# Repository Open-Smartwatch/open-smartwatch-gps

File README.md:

# Open-Smartwatch KiCAD files

Repo for kicad schematic, board and gerber files. This project is in development and is not ready for release.

Update 2025-06: There never was a release since the selected GPS module does not work on a wearable-sized PCB, and while worn at the same time.

## Tools

To view/modify the files from this repository, install KiCAD from: [https://kicad.org](https://kicad.org)

Also, add the following Symbol/Footprint library to KiCAD: [https://github.com/Open-Smartwatch/Kicad-Libraries](https://github.com/Open-Smartwatch/Kicad-Libraries)

## Schematic

## Plots

## BOM

See: [https://htmlpreview.github.io/?https://github.com/Open-Smartwatch/kicad-project/blob/master/docs/bom/osw-ibom_v.html](https://htmlpreview.github.io/?https://github.com/Open-Smartwatch/kicad-project/blob/master/docs/bom/osw-ibom_v.html)

## Instagram 
https://www.instagram.com/pauls_3d_things/

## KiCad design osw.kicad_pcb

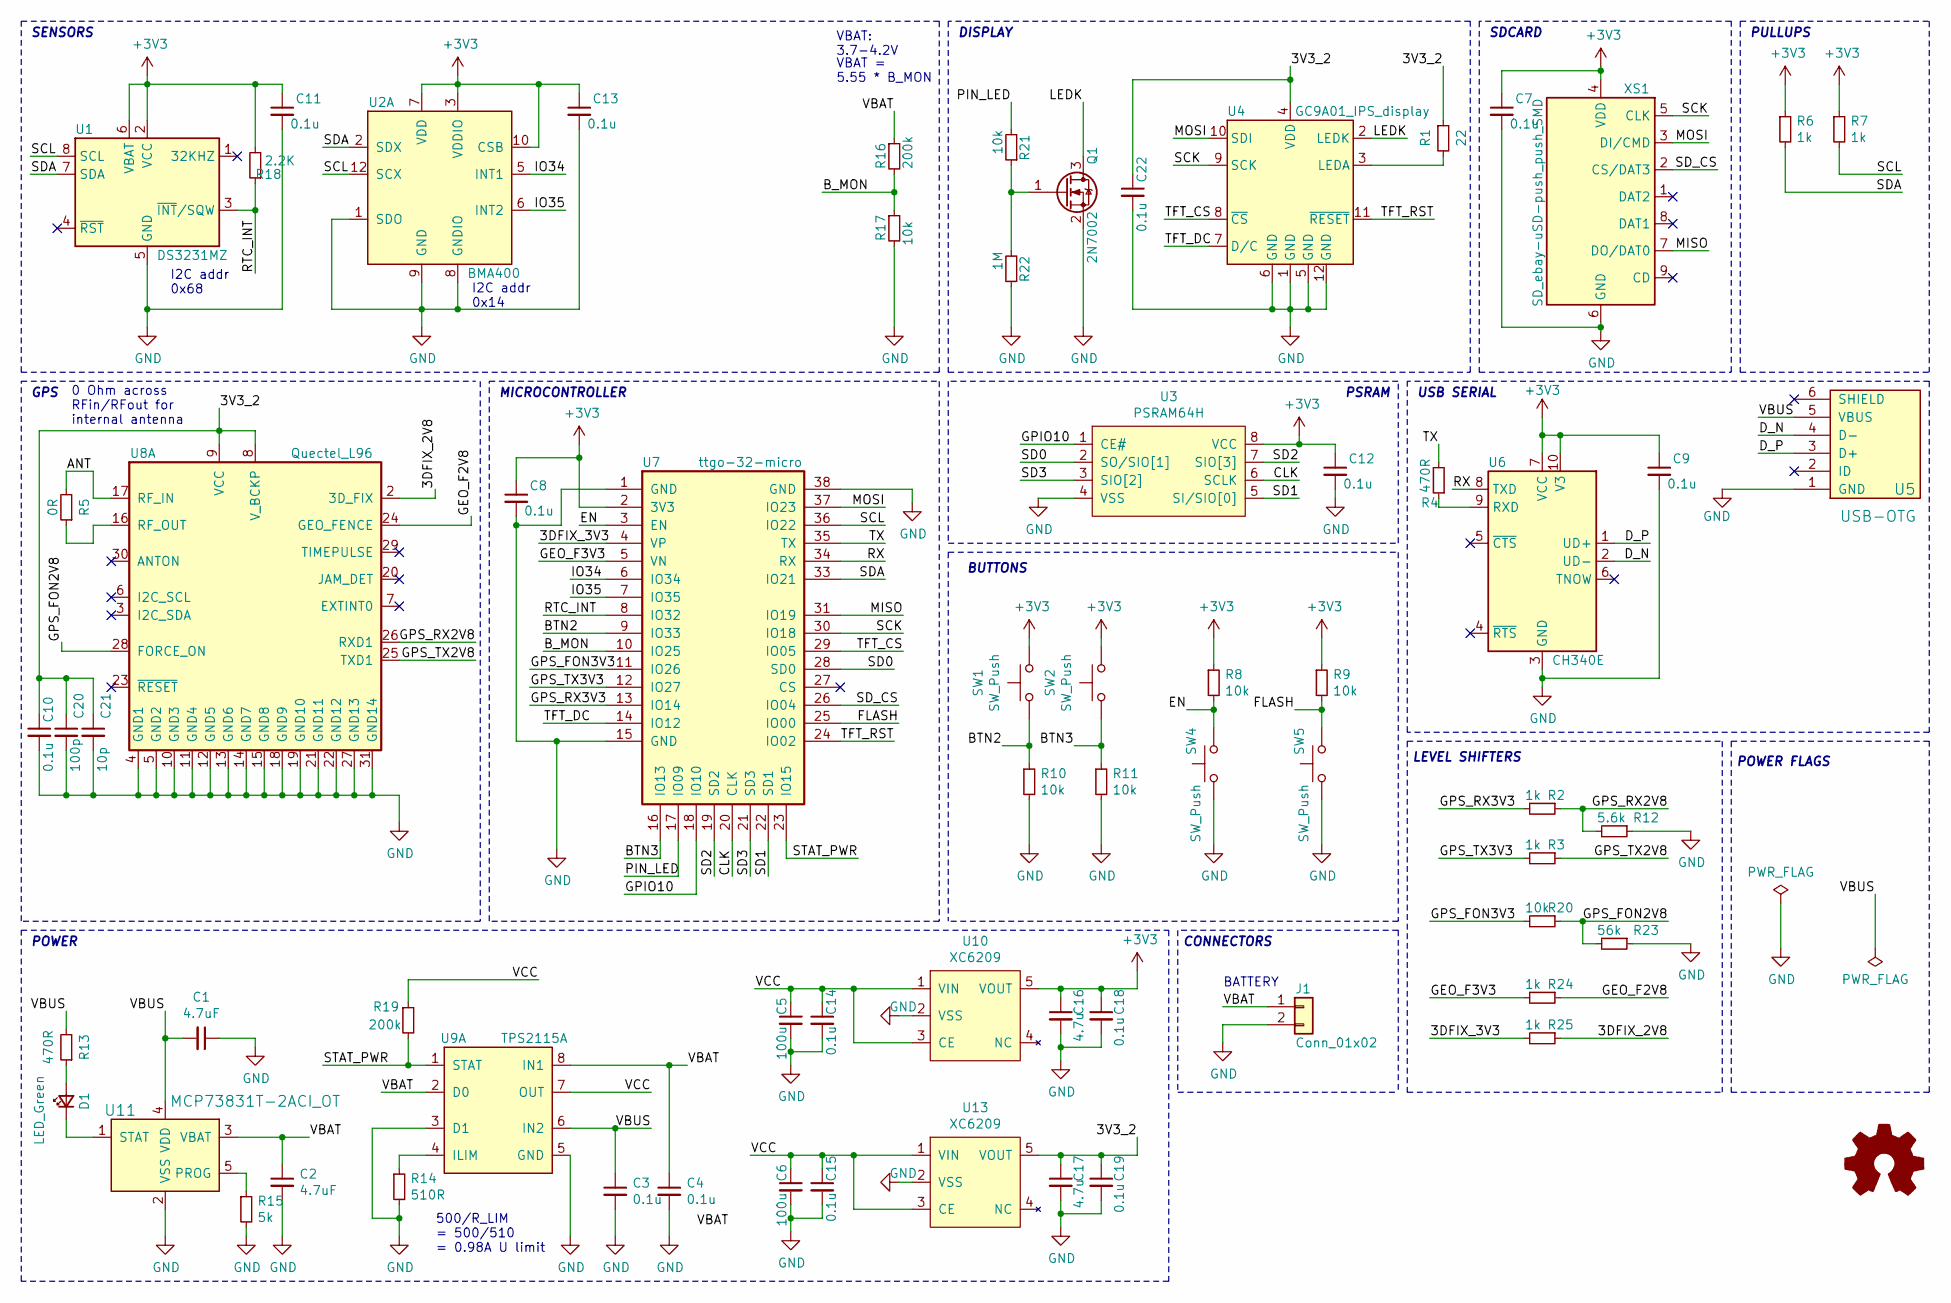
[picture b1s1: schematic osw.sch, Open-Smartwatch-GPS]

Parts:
C1, C2: 4.7uF; C_0603_1608Metric
C3, C4, C7, C8, C9, C10, C11, C12, C13, C14, C15, C18, C19, C22: 0.1u; C_0603_1608Metric
C5, C6: 100u; C_1206_3216Metric
C16, C17: 4.7u; C_0603_1608Metric
C20: 100p; C_0603_1608Metric
C21: 10p; C_0603_1608Metric
D1: LED_Green; LED_0805_2012Metric
J1: Conn_01x02; PinHeader_1x02_P2.54mm_Vertical
Q1: 2N7002; SOT-23
R1: 22; R_0603_1608Metric
R2, R3, R6, R7, R24, R25: 1k; R_0603_1608Metric
R4, R13: 470R; R_0603_1608Metric
R5: 0R; R_0402_1005Metric
R8, R9, R10, R11, R17, R20, R21: 10k; R_0603_1608Metric
R12: 5.6k; R_0603_1608Metric
R14: 510R; R_0603_1608Metric
R15: 5k; R_0603_1608Metric
R16, R19: 200k; R_0603_1608Metric
R18: 2.2K; R_0603_1608Metric
R22: 1M; R_0603_1608Metric
R23: 56k; R_0603_1608Metric
SW1, SW2, SW4, SW5: SW_Push; button_side_smd
U1: DS3231MZ; SOIC-8_3.9x4.9mm_P1.27mm
U2: BMA400; LGA-12_2x2mm_P0.5mm; MPN BMA400; DigiKey_PN 828-1081-1-ND
U3: PSRAM64H; SOP-8_3.9x4.9mm_P1.27mm
U4: GC9A01_IPS_display
U5: USB-OTG; USBmicro-B
U6: CH340E; MSOP-10_3x3mm_P0.5mm
U7: ttgo-32-micro
U8: Quectel_L96
U9: TPS2115A; TSSOP-8_4.4x3mm_P0.65mm; MPN TPS2115APWR; DigiKey_PN 296-16940-1-ND
U10, U13: XC6209; SOT-23-5
U11: MCP73831T-2ACI_OT; SOT-23-5; MPN MCP73831T-2ACI/OT; Digi-Key_PN MCP73831T-2ACI/OTCT-ND
XS1: SD_ebay-uSD-push_push_SMD; Conn_uSDcard

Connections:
+3V3: C7.1, C8.1, C9.1, C11.1, C12.1, C13.1, C16.1, C18.1, R6.1, R7.1, R8.1, R9.1, R18.2, SW1.2, SW2.2, U1.2 (VCC), U1.6 (VBAT), U2.3 (VDDIO), U2.7 (VDD), U2.10 (CSB), U3.8 (VCC), U6.7 (VCC), U6.10 (V3), U7.2 (3V3), U10.5 (VOUT), XS1.4 (VDD)
/3DFIX_2V8: R25.1, U8.2 (3D_FIX)
/3DFIX_3V3: R25.2, U7.4 (VP)
/3V3_2: C10.1, C17.1, C19.1, C20.1, C21.1, C22.1, R1.1, U4.4 (VDD), U8.8 (V_BCKP), U8.9 (VCC), U13.5 (VOUT)
/ANT: R5.2, U8.17 (RF_IN)
/BTN2: R10.1, SW1.1, U7.9 (IO33)
/BTN3: R11.1, SW2.1, U7.16 (IO13)
/B_MON: R16.2, R17.1, U7.10 (IO25)
/CLK: U3.6 (SCLK), U7.20 (CLK)
/D_N: U5.4 (D-), U6.2 (UD-)
/D_P: U5.3 (D+), U6.1 (UD+)
/EN: R8.2, SW4.2, U7.3 (EN)
/FLASH: R9.2, SW5.2, U7.25 (IO00)
/GEO_F2V8: R24.1, U8.24 (GEO_FENCE)
/GEO_F3V3: R24.2, U7.5 (VN)
/GPIO10: U3.1 (CE#), U7.18 (IO10)
/GPS_FON2V8: R20.1, R23.2, U8.28 (FORCE_ON)
/GPS_FON3V3: R20.2, U7.11 (IO26)
/GPS_RX2V8: R2.1, R12.2, U8.26 (RXD1)
/GPS_RX3V3: R2.2, U7.13 (IO14)
/GPS_TX2V8: R3.1, U8.25 (TXD1)
/GPS_TX3V3: R3.2, U7.12 (IO27)
/IO34: U2.5 (INT1), U7.6 (IO34)
/IO35: U2.6 (INT2), U7.7 (IO35)
/LEDK: Q1.3 (D), U4.2 (LEDK)
/MISO: U7.31 (IO19), XS1.7 (DO/DAT0)
/MOSI: U4.10 (SDI), U7.37 (IO23), XS1.3 (DI/CMD)
/PIN_LED: R21.2, U7.17 (IO09)
/RTC_INT: R18.1, U1.3 (~INT~/SQW), U7.8 (IO32)
/RX: U6.8 (TXD), U7.34 (RX)
/SCK: U4.9 (SCK), U7.30 (IO18), XS1.5 (CLK)
/SCL: R7.2, U1.8 (SCL), U2.12 (SCX), U7.36 (IO22)
/SD0: U3.2 (SO/SIO[1]), U7.28 (SD0)
/SD1: U3.5 (SI/SIO[0]), U7.22 (SD1)
/SD2: U3.7 (SIO[3]), U7.19 (SD2)
/SD3: U3.3 (SIO[2]), U7.21 (SD3)
/SDA: R6.2, U1.7 (SDA), U2.2 (SDX), U7.33 (IO21)
/SD_CS: U7.26 (IO04), XS1.2 (CS/DAT3)
/STAT_PWR: R19.2, U7.23 (IO15), U9.1 (STAT)
/TFT_CS: U4.8 (~CS), U7.29 (IO05)
/TFT_DC: U4.7 (D/C), U7.14 (IO12)
/TFT_RST: U4.11 (~RESET), U7.24 (IO02)
/TX: R4.2, U7.35 (TX)
/VBAT: C2.1, C4.1, J1.1, R16.1, U9.2 (D0), U9.8 (IN1), U11.3 (VBAT)
/VBUS: C1.2, C3.1, R13.2, U5.5 (VBUS), U9.6 (IN2), U11.4 (VDD)
/VCC: C5.1, C6.1, C14.1, C15.1, R19.1, U9.7 (OUT), U10.1 (VIN), U10.3 (CE), U13.1 (VIN), U13.3 (CE)
GND: C1.1, C2.2, C3.2, C4.2, C5.2, C6.2, C7.2, C8.2, C9.2, C10.2, C11.2, C12.2, C13.2, C14.2, C15.2, C16.2, C17.2, C18.2, C19.2, C20.2, C21.2, C22.2, J1.2, Q1.2 (S), R10.2, R11.2, R12.1, R14.2, R15.2, R17.2, R22.1, R23.1, SW4.1, SW5.1, U1.5 (GND), U2.1 (SDO), U2.8 (GNDIO), U2.9 (GND), U3.4 (VSS), U4.1 (GND), U4.5 (GND), U4.6 (GND), U4.12 (GND), U5.1 (GND), U6.3 (GND), U7.1 (GND), U7.15 (GND), U7.38 (GND), U8.4 (GND1), U8.5 (GND2), U8.10 (GND3), U8.11 (GND4), U8.12 (GND5), U8.13 (GND6), U8.14 (GND7), U8.15 (GND8), U8.18 (GND9), U8.19 (GND10), U8.21 (GND11), U8.22 (GND12), U8.27 (GND13), U8.31 (GND14), U9.3 (D1), U9.5 (GND), U10.2 (VSS), U11.2 (VSS), U13.2 (VSS), XS1.6 (GND)
unnamed: D1.1 (K), U11.1 (STAT)
unnamed: D1.2 (A), R13.1
unnamed: Q1.1 (G), R21.1, R22.2
unnamed: R1.2, U4.3 (LEDA)
unnamed: R4.1, U6.9 (RXD)
unnamed: R5.1, U8.16 (RF_OUT)
unnamed: R14.1, U9.4 (ILIM)
unnamed: R15.1, U11.5 (PROG)

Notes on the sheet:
500/R_LIM = 500/510 = 0.98A U limit
GPS
SENSORS
POWER
SDCARD
DISPLAY
USB SERIAL
BUTTONS
PULLUPS
0 Ohm across RFin/RFout for internal antenna
VBAT: 3.7-4.2V
VBAT = 5.55 * B_MON
MICROCONTROLLER
POWER FLAGS
I2C addr 0x68
I2C addr 0x14
CONNECTORS
BATTERY
LEVEL SHIFTERS
PSRAM

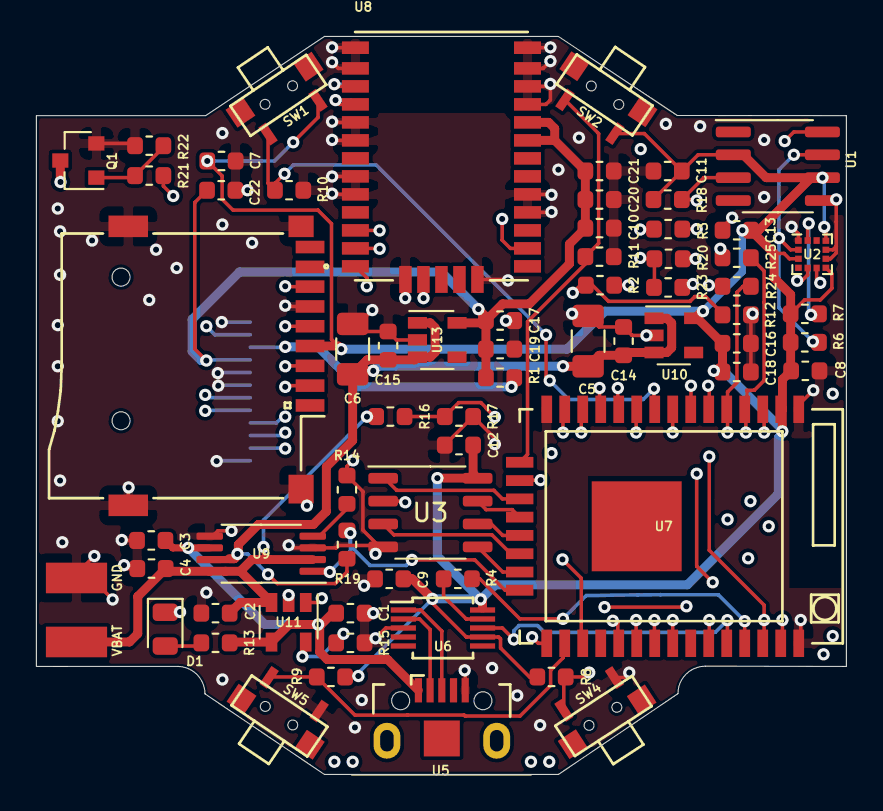
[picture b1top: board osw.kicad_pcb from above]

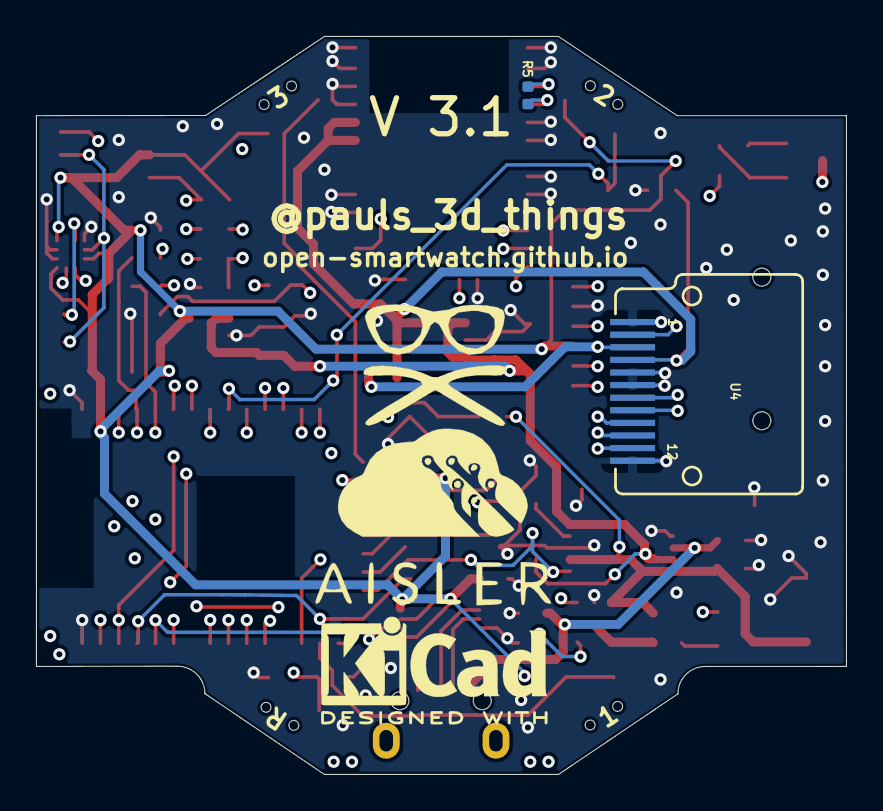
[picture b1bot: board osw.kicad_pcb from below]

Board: 4 copper layers, 45.0 x 41.0 mm, 67 parts (2 on the bottom side), 55 nets.

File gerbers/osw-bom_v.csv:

Reference,Value,Package,Quantity,digikey_pn,mpn,manufacturer,digi-key_pn,manf,manf#
"Unpolarized capacitor, small symbol",10p,C_0603_1608Metric,1,,,,,,
"Unpolarized capacitor, small symbol",100p,C_0603_1608Metric,1,,,,,,
"Unpolarized capacitor, small symbol",0.1u,C_0603_1608Metric,1,,,,,,
"Unpolarized capacitor, small symbol",0.1u,C_0603_1608Metric,1,,,,,,
"Unpolarized capacitor, small symbol",0.1u,C_0603_1608Metric,1,,,,,,
"Unpolarized capacitor, small symbol",0.1u,C_0603_1608Metric,1,,,,,,
"Unpolarized capacitor, small symbol",0.1u,C_0603_1608Metric,1,,,,,,
"Unpolarized capacitor, small symbol",0.1u,C_0603_1608Metric,1,,,,,,
"Unpolarized capacitor, small symbol",0.1u,C_0603_1608Metric,1,,,,,,
"Unpolarized capacitor, small symbol",0.1u,C_0603_1608Metric,1,,,,,,
"Unpolarized capacitor, small symbol",0.1u,C_0603_1608Metric,1,,,,,,
"Unpolarized capacitor, small symbol",0.1u,C_0603_1608Metric,1,,,,,,
"Unpolarized capacitor, small symbol",0.1u,C_0603_1608Metric,1,,,,,,
"Unpolarized capacitor, small symbol",0.1u,C_0603_1608Metric,1,,,,,,
"Unpolarized capacitor, small symbol",0.1u,C_0603_1608Metric,1,,,,,,
"Unpolarized capacitor, small symbol",0.1u,C_0603_1608Metric,1,,,,,,
"Unpolarized capacitor, small symbol",4.7uF,C_0603_1608Metric,1,,,,,,
"Unpolarized capacitor, small symbol",4.7u,C_0603_1608Metric,1,,,,,,
"Unpolarized capacitor, small symbol",4.7u,C_0603_1608Metric,1,,,,,,
"Unpolarized capacitor, small symbol",4.7uF,C_0603_1608Metric,1,,,,,,
"Unpolarized capacitor, small symbol",100u,C_1206_3216Metric,1,,,,,,
"Unpolarized capacitor, small symbol",100u,C_1206_3216Metric,1,,,,,,
"Light emitting diode, small symbol",LED_Green,LED_0805_2012Metric,1,,,,,,
"Generic connector, single row, 01x02, script generated (kicad-library-utils/schlib/autogen/connector/)",Conn_01x02,PinHeader_1x02_P2.54mm_Vertical,1,,,,,,
"0.115A Id, 60V Vds, N-Channel MOSFET, SOT-23",2N7002,SOT-23,1,,,,,,
"Resistor, small symbol",0R,R_0402_1005Metric,1,,,,,,
"Resistor, small symbol",22,R_0603_1608Metric,1,,,,,,
"Resistor, small symbol",470R,R_0603_1608Metric,1,,,,,,
"Resistor, small symbol",470R,R_0603_1608Metric,1,,,,,,
"Resistor, small symbol",510R,R_0603_1608Metric,1,,,,,,
"Resistor, small symbol",1k,R_0603_1608Metric,1,,,,,,
"Resistor, small symbol",1k,R_0603_1608Metric,1,,,,,,
"Resistor, small symbol",1k,R_0603_1608Metric,1,,,,,,
"Resistor, small symbol",1k,R_0603_1608Metric,1,,,,,,
"Resistor, small symbol",1k,R_0603_1608Metric,1,,,,,,
"Resistor, small symbol",1k,R_0603_1608Metric,1,,,,,,
"Resistor, small symbol",2.2K,R_0603_1608Metric,1,,,,,,
"Resistor, small symbol",5k,R_0603_1608Metric,1,,,,,,
"Resistor, small symbol",5.6k,R_0603_1608Metric,1,,,,,,
"Resistor, small symbol",10k,R_0603_1608Metric,1,,,,,,
"Resistor, small symbol",10k,R_0603_1608Metric,1,,,,,,
"Resistor, small symbol",10k,R_0603_1608Metric,1,,,,,,
"Resistor, small symbol",10k,R_0603_1608Metric,1,,,,,,
"Resistor, small symbol",10k,R_0603_1608Metric,1,,,,,,
"Resistor, small symbol",10k,R_0603_1608Metric,1,,,,,,
"Resistor, small symbol",10k,R_0603_1608Metric,1,,,,,,
"Resistor, small symbol",56k,R_0603_1608Metric,1,,,,,,
"Resistor, small symbol",200k,R_0603_1608Metric,1,,,,,,
"Resistor, small symbol",200k,R_0603_1608Metric,1,,,,,,
"Resistor, small symbol",1M,R_0603_1608Metric,1,,,,,,
"Push button switch, generic, two pins",SW_Push,button_side_smd,1,,,,,,
"Push button switch, generic, two pins",SW_Push,button_side_smd,1,,,,,,
"Push button switch, generic, two pins",SW_Push,button_side_smd,1,,,,,,
"Push button switch, generic, two pins",SW_Push,button_side_smd,1,,,,,,
,BMA400,LGA-12_2x2mm_P0.5mm,1,828-1081-1-ND,BMA400,Bosch Sensortec,,,
,CH340E,MSOP-10_3x3mm_P0.5mm,1,,,,,,
"±5ppm, I2C Real-Time Clock SOIC-8",DS3231MZ,SOIC-8_3.9x4.9mm_P1.27mm,1,,,,,,
,GC9A01_IPS_display,GC9A01_IPS_display,1,,,,,,
,MCP73831T-2ACI_OT,SOT-23-5,1,,MCP73831T-2ACI/OT,Microchip Technology,MCP73831T-2ACI/OTCT-ND,,
,PSRAM64H,SOP-8_3.9x4.9mm_P1.27mm,1,,,,,,
,Quectel_L96,Quectel_L96,1,,,,,,
,TPS2115A,TSSOP-8_4.4x3mm_P0.65mm,1,296-16940-1-ND,TPS2115APWR,Texas Instruments,,,
,USB-OTG,USBmicro-B,1,,,,,,
,XC6209,SOT-23-5,1,,,,,,
,XC6209,SOT-23-5,1,,,,,,
,ttgo-32-micro,ttgo-32-micro,1,,,,,,
,SD_ebay-uSD-push_push_SMD,Conn_uSDcard,1,,,,,ebay,_

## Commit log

2020-11-16 kicad-export
2021-01-14 Update LICENSE
2021-02-12 finalize rev 3.0
2021-02-18 rev 3.1 - remove pull up - fix ttgo32 footprint
2021-02-18 fix page metadata
2021-10-22 update readme.md
    update readme.md
